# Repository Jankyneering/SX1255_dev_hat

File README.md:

# SX1255 Dev Hat

A Simple Raspberry Pi Zero shield with the SX1255 RF transceiver chip.  
[`v0.1`](https://github.com/Jankyneering/SX1255_dev_hat/releases/tag/v0.1) based on [M17](https://github.com/M17-Project/SX1255_HAT-hw/blob/main/README.md)'s design, and Semtech's application schematic in the [SX1255 Datasheet](https://www.semtech.com/uploads/documents/sx1255.pdf).

## Production files

Production files for this hat can be found in the [releases](https://github.com/Jankyneering/SX1255_dev_hat/releases). Upload these files to your favorite PCB manufacturer, and make sure to specify the correct board thickness (1.6mm).  
We ordered a batch from JLCPCB and had them assemble the components.

> v0.1 is not intended for production use, but rather as a development platform for testing the SX1255 chip and its software support. It is not optimized for performance, power consumption, RF impedance, and may have some design flaws. Use at your own risk.

## License & Acknowledgements

Made with ❤️, lots of ☕️, and lack of 🛌  
Published under CreativeCommons BY-SA 4.0

This work is licensed under a [Creative Commons Attribution-ShareAlike 4.0 International License](http://creativecommons.org/licenses/by-sa/4.0/).

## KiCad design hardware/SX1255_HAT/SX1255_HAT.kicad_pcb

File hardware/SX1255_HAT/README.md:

# SX1255_HAT

Raspberry Pi Zero shield with the SX1255 RF transceiver chip.  
Based on [M17](https://github.com/M17-Project/SX1255_HAT-hw/blob/main/README.md)'s design.

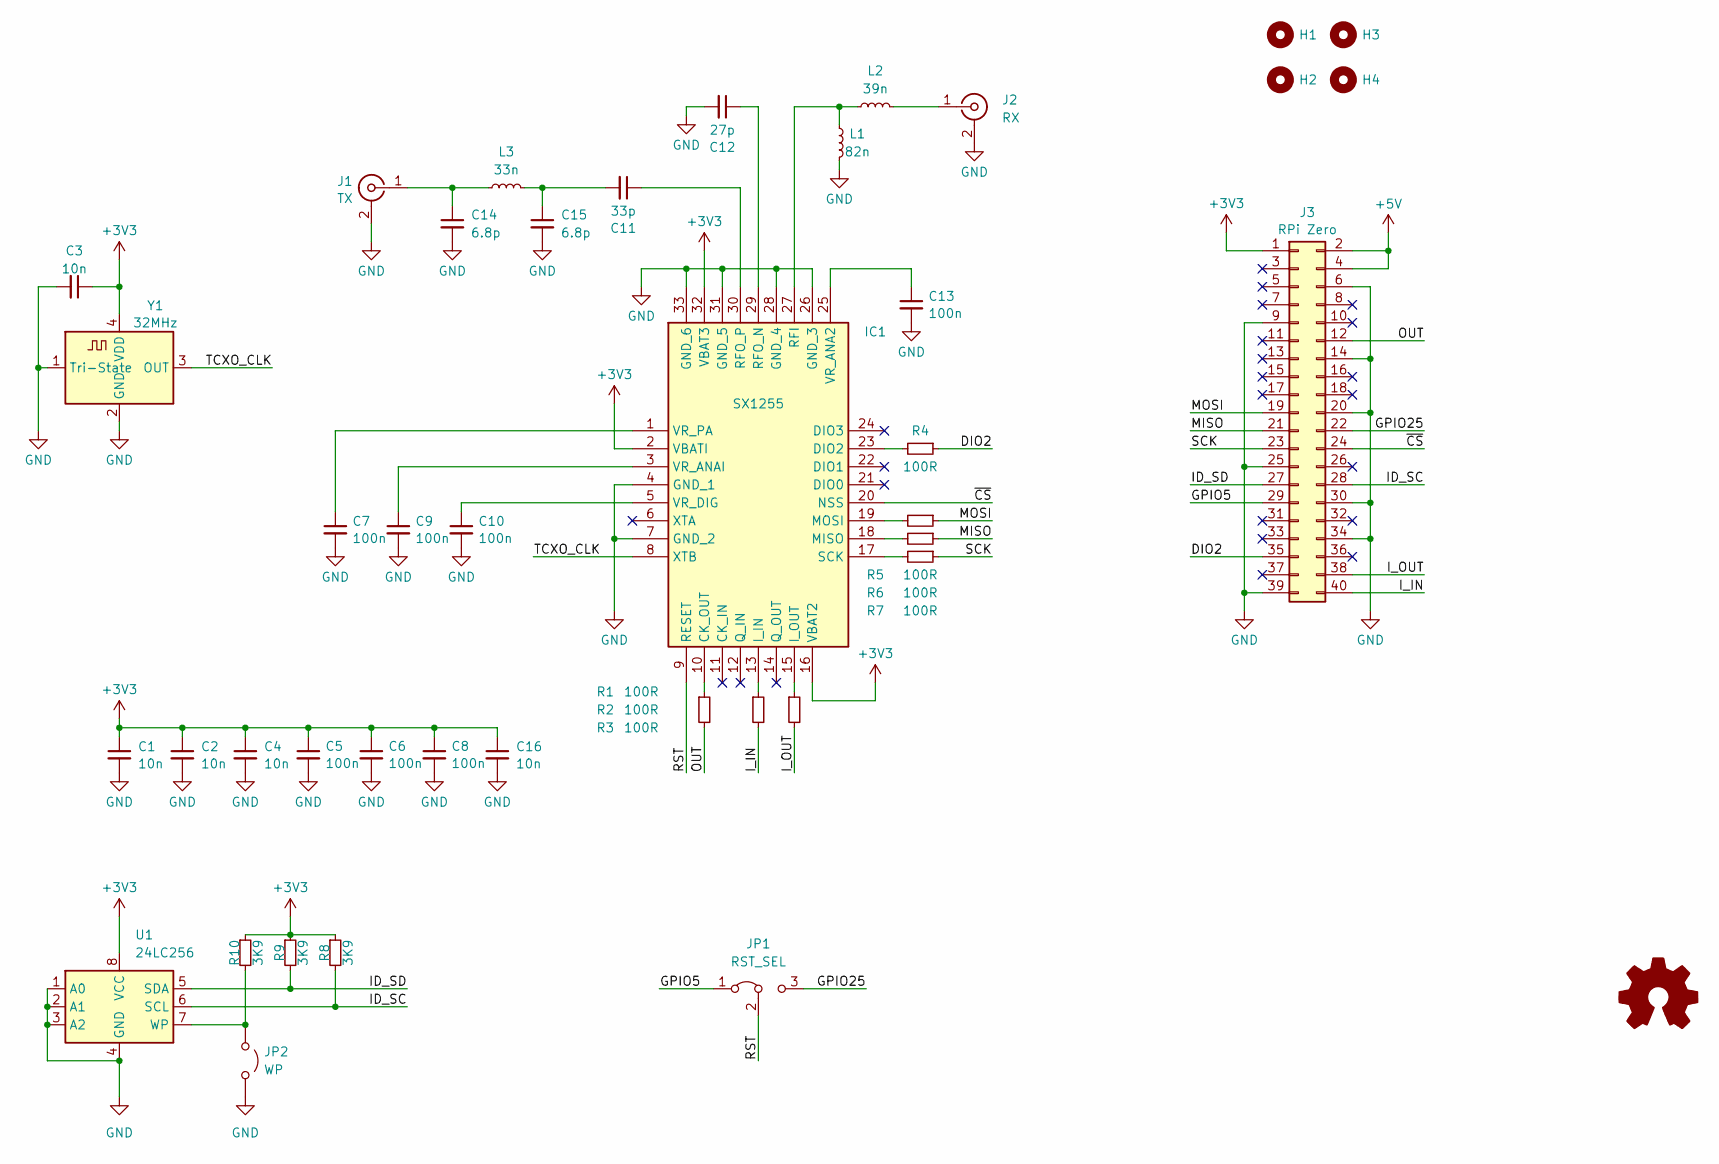
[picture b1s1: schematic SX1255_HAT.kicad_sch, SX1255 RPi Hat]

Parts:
C1, C2, C3, C4, C16: 10n; C_0603_1608Metric; MPN C0603C103M4REC7411
C5, C6, C7, C8, C9, C10, C13: 100n; C_0603_1608Metric; MPN 06035G104ZAT2A
C11: 33p; C_0603_1608Metric; MPN VJ0603A330KXAPW1BC
C12: 27p; C_0603_1608Metric; MPN AC0603JRNPO9BN270
C14, C15: 6.8p; C_0603_1608Metric; MPN 06035G104ZAT2A
H1, H2, H3, H4: MountingHole; MountingHole_2.7mm_M2.5_DIN965
IC1: SX1255; QFN50P500X500X80-33N-D; MPN SX1255IWLTRT
J1: TX; U.FL_Molex_MCRF_73412-0110_Vertical; MPN RF2-04A-T-00-50-G
J2: RX; U.FL_Molex_MCRF_73412-0110_Vertical; MPN RF2-04A-T-00-50-G
J3: RPi Zero; PinSocket_2x20_P2.54mm_Vertical
JP1: RST_SEL; SolderJumper-3_P1.3mm_Bridged12_RoundedPad1.0x1.5mm_NumberL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
JP2: WP; SolderJumper-2_P1.3mm_Open_RoundedPad1.0x1.5mm
L1: 82n; L_0603_1608Metric; MPN AISC-0603-R082J-T
L2: 39n; L_0603_1608Metric; MPN AISC-0603-R039J-T
L3: 33n; L_0603_1608Metric; MPN AISC-0603-R039J-T
R1, R2, R3, R4, R5, R6, R7: 100R; R_0603_1608Metric; MPN CRCW0603100RFKECC
R8, R9, R10: 3K9; R_0603_1608Metric; MPN CRCW06033K9FKECC
SYM1: Logo_Open_Hardware_Small; OSHW-Logo2_7.3x6mm_SilkScreen
U1: 24LC256; SOIC-8_3.9x4.9mm_P1.27mm
Y1: 32MHz; Crystal_SMD_2016-4Pin_2.0x1.6mm; MPN ECS-TXO-20CSMV4-320-AY-TR

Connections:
+3V3: C1.1, C2.1, C3.1, C4.1, C5.1, C6.1, C8.1, C16.1, IC1.2 (VBATI), IC1.16 (VBAT2), IC1.32 (VBAT3), J3.1, R8.1, R9.1, R10.1, U1.8 (VCC), Y1.4 (VDD)
+5V: J3.2, J3.4
/DIO2: J3.35, R4.1
/GPIO5: J3.29, JP1.1 (A)
/GPIO25: J3.22, JP1.3 (B)
/ID_SC: J3.28, R8.2, U1.6 (SCL)
/ID_SD: J3.27, R9.2, U1.5 (SDA)
/I_IN: J3.40, R2.2
/I_OUT: J3.38, R3.2
/MISO: J3.21, R6.1
/MOSI: J3.19, R5.1
/OUT: J3.12, R1.2
/RST: IC1.9 (RESET), JP1.2 (C)
/SCK: J3.23, R7.1
/TCXO_CLK: IC1.8 (XTB), Y1.3 (OUT)
/~CS: IC1.20 (NSS), J3.24
GND: C1.2, C2.2, C3.2, C4.2, C5.2, C6.2, C7.2, C8.2, C9.2, C10.2, C12.2, C13.2, C14.2, C15.2, C16.2, IC1.4 (GND_1), IC1.7 (GND_2), IC1.26 (GND_3), IC1.28 (GND_4), IC1.31 (GND_5), IC1.33 (GND_6), J1.2 (Ext), J2.2 (Ext), J3.6, J3.9, J3.14, J3.20, J3.25, J3.30, J3.34, J3.39, JP2.2 (B), L1.1, U1.1 (A0), U1.2 (A1), U1.3 (A2), U1.4 (GND), Y1.1 (Tri-State), Y1.2 (GND)
unnamed: C11.2, C15.1, L3.1
unnamed: IC1.10 (CK_OUT), R1.1
unnamed: IC1.23 (DIO2), R4.2
unnamed: IC1.13 (I_IN), R2.1
unnamed: IC1.15 (I_OUT), R3.1
unnamed: IC1.18 (MISO), R6.2
unnamed: IC1.19 (MOSI), R5.2
unnamed: IC1.27 (RFI), L1.2, L2.2
unnamed: C12.1, IC1.29 (RFO_N)
unnamed: C11.1, IC1.30 (RFO_P)
unnamed: IC1.17 (SCK), R7.2
unnamed: C13.1, IC1.25 (VR_ANA2)
unnamed: C9.1, IC1.3 (VR_ANAI)
unnamed: C10.1, IC1.5 (VR_DIG)
unnamed: C7.1, IC1.1 (VR_PA)
unnamed: C14.1, J1.1 (In), L3.2
unnamed: J2.1 (In), L2.1
unnamed: JP2.1 (A), R10.2, U1.7 (WP)

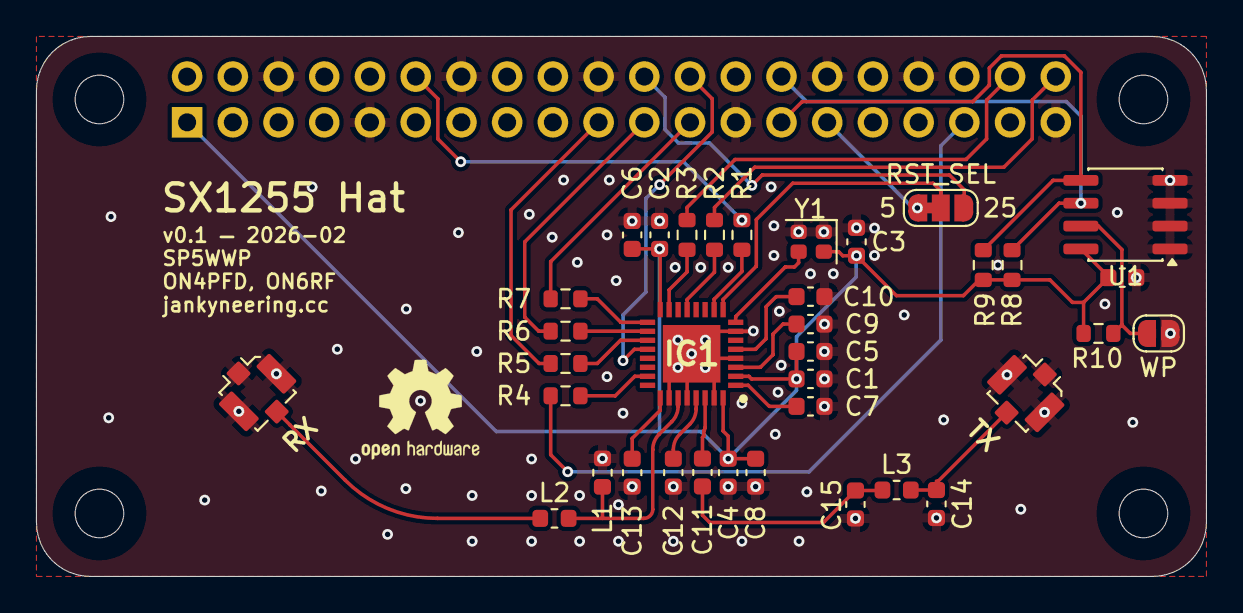
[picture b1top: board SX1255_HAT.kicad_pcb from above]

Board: 2 copper layers, 65.0 x 30.0 mm, 42 parts (1 on the bottom side), 35 nets.

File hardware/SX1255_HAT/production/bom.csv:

Designator,Footprint,Quantity,Value,LCSC Part #
"C1, C16, C2, C3, C4",0603,5,10n,C0603C103M4REC7411
"C10, C13, C5, C6, C7, C8, C9",0603,7,100n,06035G104ZAT2A
C11,0603,1,33p,VJ0603A330KXAPW1BC
C12,0603,1,27p,AC0603JRNPO9BN270
"C14, C15",0603,2,6.8p,06035G104ZAT2A
IC1,QFN50P500X500X80-33N-D,1,SX1255,SX1255IWLTRT
J1,U.FL_Molex_MCRF_73412-0110_Vertical,1,TX,RF2-04A-T-00-50-G
J2,U.FL_Molex_MCRF_73412-0110_Vertical,1,RX,RF2-04A-T-00-50-G
JP2,SolderJumper-2_P1.3mm_Open_RoundedPad1.0x1.5mm,1,WP,
L1,0603,1,82n,AISC-0603-R082J-T
L2,0603,1,39n,AISC-0603-R039J-T
L3,0603,1,33n,AISC-0603-R039J-T
"R1, R2, R3, R4, R5, R6, R7",0603,7,100R,CRCW0603100RFKECC
"R10, R8, R9",0603,3,3K9,CRCW06033K9FKECC
U1,SOIC-8_3.9x4.9mm_P1.27mm,1,24LC256,
Y1,Crystal_SMD_2016-4Pin_2.0x1.6mm,1,32MHz,ECS-TXO-20CSMV4-320-AY-TR

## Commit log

2026-02-16 added base repo files
2026-02-16 added sources
2026-02-16 updated shield
2026-02-16 linted markdown
2026-02-16 Added Tx filters, EEPROM, modified for soapy-sx compat
2026-02-16 Added decoupling for EEPROM and WP pin
2026-02-16 renamed license file
2026-02-16 added DRU, modified component placement, updated schematic
2026-02-17 added fabrication files
2026-02-17 added info on README
2026-02-17 added link to `v0.1` release

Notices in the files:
hardware/SX1255_HAT/README.md:
CC BY-NC-SA 4.0
